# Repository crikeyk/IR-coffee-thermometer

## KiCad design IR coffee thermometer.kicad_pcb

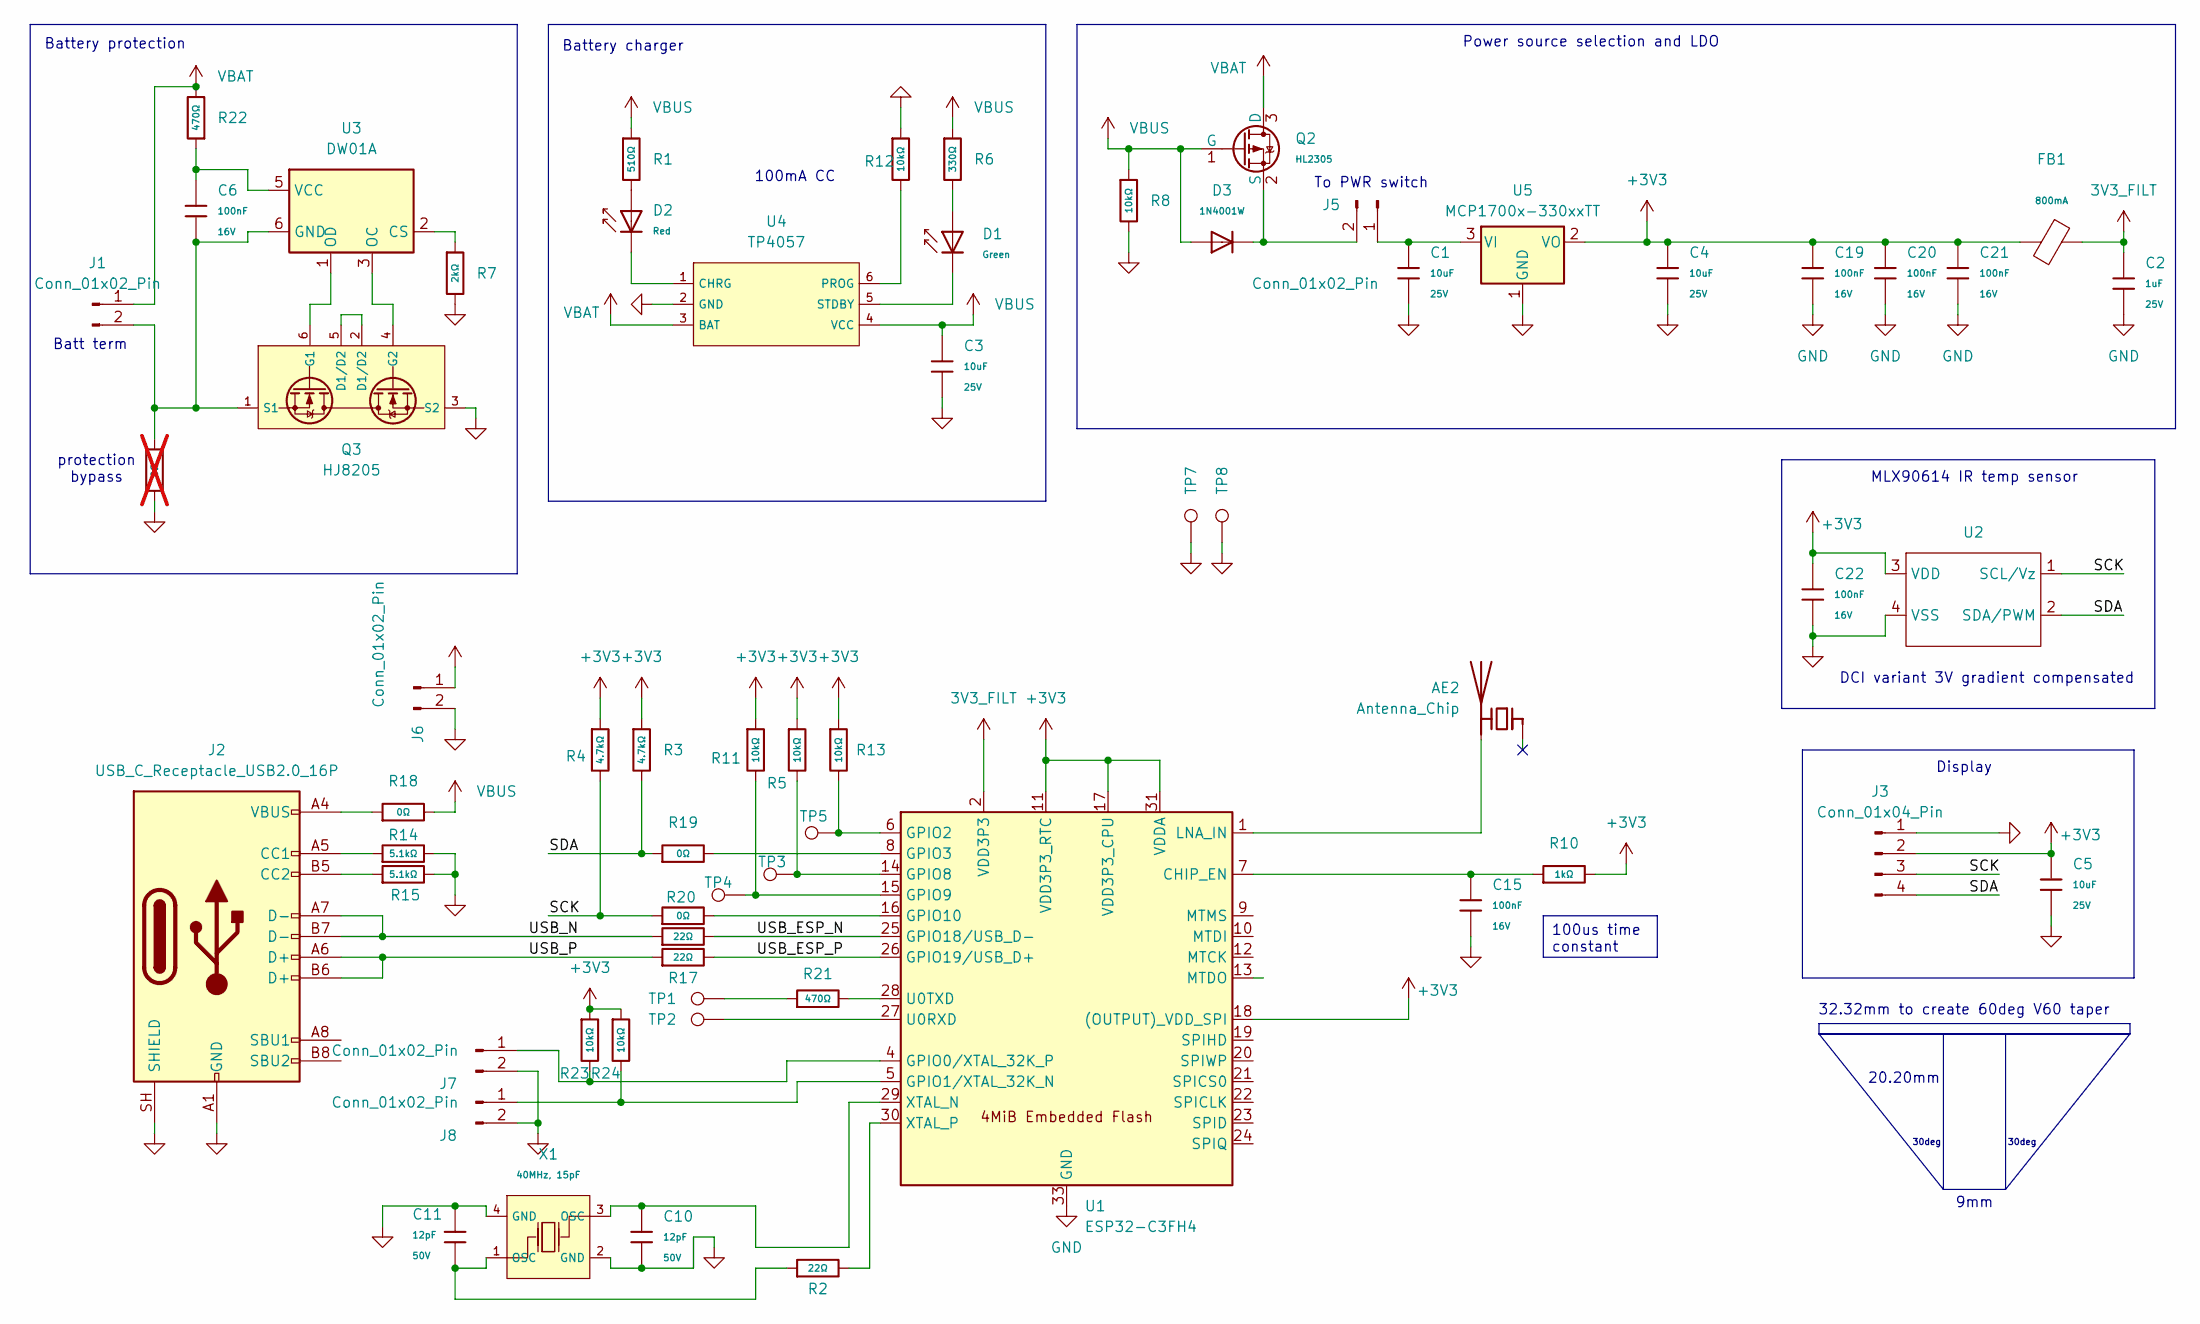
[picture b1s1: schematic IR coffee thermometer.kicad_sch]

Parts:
AE2: Antenna_Chip; C_1206_3216Metric; LCSC C127629
C1, C3, C4, C5: 10uF; C_0603; Voltage Rated 25V; Tolerance ±20%; Part CL10A106MA8NRNC; LCSC C96446
C2: 1uF; C_0402; Voltage Rated 25V; Tolerance ±10%; Part CL05A105KA5NQNC; LCSC C52923
C6, C15, C19, C20, C21, C22: 100nF; C_0402; Voltage Rated 16V; Tolerance ±10%; Part CL05B104KO5NNNC; LCSC C1525
C10, C11: 12pF; C_0402; Voltage Rated 50V; Tolerance ±5%; Part 0402CG120J500NT; LCSC C1547
D1: Green; D_0805; Part KT-0805G; LCSC C2297
D2: Red; D_0805; Forward Voltage (VF) 1.6V~2.6V; Part NCD0805R1; LCSC C84256
D3: 1N4001W; D_SOD-123FL; Voltage - Forward(Vf@If) 1V@1.0A; Voltage - DC Reverse(Vr) 50V; Part 1N4001W; LCSC C18199085
FB1: FB_0805; Current Rating 800mA; Tolerance ±25%; Part GZ2012D101TF; LCSC C1015
J1, J5, J6, J7, J8: Conn_01x02_Pin; TestPoint_2Pads_Pitch2.54mm_Drill0.8mm
J2: USB_C_Receptacle_USB2.0_16P; USB_C_Receptacle_HRO_TYPE-C-31-M-12; LCSC C165948
J3: Conn_01x04_Pin; PinSocket_1x04_P2.54mm_Vertical; LCSC C2718488
Q2: HL2305; Q_SOT-23; Part HL2305; LCSC C28646261
Q3: HJ8205; SOT-23-6_L2.9-W1.6-P0.95-LS2.8-BR; Part HJ8205; LCSC C20069150
R1: 510Ω; R_0402; Overload Voltage (Max) 50V; Tolerance ±1%; Part 0402WGF5100TCE; LCSC C25123
R2, R16, R17: 22Ω; R_0402; Overload Voltage (Max) 50V; Tolerance ±1%; Part 0402WGF220JTCE; LCSC C25092
R3, R4: 4.7kΩ; R_0402; Overload Voltage (Max) 50V; Tolerance ±1%; Part 0402WGF4701TCE; LCSC C25900
R5, R8, R11, R12, R13, R23, R24: 10kΩ; R_0402; Overload Voltage (Max) 50V; Tolerance ±1%; Part 0402WGF1002TCE; LCSC C25744
R6: 330Ω; R_0402; Overload Voltage (Max) 50V; Tolerance ±1%; Part 0402WGF3300TCE; LCSC C25104
R7: 2kΩ; R_0402; Overload Voltage (Max) 50V; Tolerance ±1%; Part 0402WGF2001TCE; LCSC C4109
R9: 0Ω; R_0402; Overload Voltage (Max) 50V; Tolerance ±1%; Part 0402WGF0000TCE; LCSC C17168; not fitted
R10: 1kΩ; R_0402; Overload Voltage (Max) 50V; Tolerance ±1%; Part 0402WGF1001TCE; LCSC C11702
R14, R15: 5.1kΩ; R_0402; Overload Voltage (Max) 50V; Tolerance ±1%; Part 0402WGF5101TCE; LCSC C25905
R18, R19, R20: 0Ω; R_0402; Overload Voltage (Max) 50V; Tolerance ±1%; Part 0402WGF0000TCE; LCSC C17168
R21, R22: 470Ω; R_0402; Overload Voltage (Max) 50V; Tolerance ±1%; Part 0402WGF4700TCE; LCSC C25117
TP1, TP2, TP3, TP4, TP5, TP7, TP8: TestPoint; TestPoint_Pad_D1.0mm
U1: ESP32-C3FH4; QFN-32-1EP_5x5mm_P0.5mm_EP3.7x3.7mm_ThermalVias; LCSC C2858491
U2: MLX90614
U3: DW01A; SOT-23-6; LCSC C18164398
U4: TP4057; SOT-23-6_L2.9-W1.6-P0.95-LS2.8-BL; Part TP4057-42-SOT26-R; LCSC C12044
U5: MCP1700x-330xxTT; SOT-23; LCSC C39051
X1: 40MHz, 15pF; OSC-SMD_4P-L3.2-W2.5-BL_SIT8008BI; PartID X322540MPB4SI; LCSC C9010

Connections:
3V3_FILT: C2.1, FB1.1, U1.2 (VDD3P3), U1.3 (VDD3P3)
+3V3: C4.1, C5.1, C19.1, C20.1, C21.1, C22.1, FB1.2, J3.2, R3.1, R4.1, R5.1, R10.2, R11.1, R13.1, R23.1, R24.1, U1.11 (VDD3P3_RTC), U1.17 (VDD3P3_CPU), U1.18 ((OUTPUT)_VDD_SPI), U1.31 (VDDA), U1.32 (VDDA), U2.3 (VDD), U5.2 (VO)
/SCK: J3.3, R4.2, R20.1, U2.1 (SCL/Vz)
/SDA: J3.4, R3.2, R19.1, U2.2 (SDA/PWM)
/USB_ESP_N: R16.2, U1.25 (GPIO18/USB_D-)
/USB_ESP_P: R17.2, U1.26 (GPIO19/USB_D+)
/USB_N: J2.A7 (D-), J2.B7 (D-), R16.1
/USB_P: J2.A6 (D+), J2.B6 (D+), R17.1
GND: C1.2, C2.2, C3.2, C4.2, C5.2, C10.2, C11.2, C15.2, C19.2, C20.2, C21.2, C22.2, J2.A1 (GND), J2.A12 (GND), J2.B1 (GND), J2.B12 (GND), J2.SH (SHIELD), J3.1, J6.2, J7.2, J8.2, Q3.3 (S2), R7.2, R8.2, R9.2, R12.1, R14.2, R15.2, TP7.1 (1_1), TP8.1 (1_1), U1.33 (GND), U2.4 (VSS), U4.2 (GND), U5.1 (GND), X1.2 (GND), X1.4 (GND)
unnamed: AE2.2 (PCB_Trace_2), U1.1 (LNA_IN)
unnamed: C11.1, R2.1, X1.1 (OSC)
unnamed: D1.2, R6.2
unnamed: D2.2, R1.2
unnamed: C6.2, J1.2, Q3.1 (S1), R9.1, U3.6 (GND)
unnamed: J2.A5 (CC1), R14.1
unnamed: J2.B5 (CC2), R15.1
unnamed: J2.A4 (VBUS), J2.A9 (VBUS), J2.B4 (VBUS), J2.B9 (VBUS), R18.1
unnamed: C1.1, J5.1, U5.3 (VI)
unnamed: D3.1, J5.2, Q2.2 (S)
unnamed: J7.1, R23.2, U1.4 (GPIO0/XTAL_32K_P)
unnamed: J8.1, R24.2, U1.5 (GPIO1/XTAL_32K_N)
unnamed: Q3.2 (D1/D2), Q3.5 (D1/D2)
unnamed: Q3.6 (G1), U3.1 (OD)
unnamed: Q3.4 (G2), U3.3 (OC)
unnamed: R21.1, TP1.1 (1_1)
unnamed: C15.1, R10.1, U1.7 (CHIP_EN)
unnamed 26: R13.2, TP5.1, U1.6 (GPIO2); also elsewhere on the board
unnamed: R19.2, U1.8 (GPIO3)
unnamed 28: R5.2, TP3.1, U1.14 (GPIO8); also elsewhere on the board
unnamed 29: R11.2, TP4.1, U1.15 (GPIO9); also elsewhere on the board
unnamed: R20.2, U1.16 (GPIO10)
unnamed: TP2.1 (1_1), U1.27 (U0RXD)
unnamed: R21.2, U1.28 (U0TXD)
unnamed: C10.1, U1.29 (XTAL_N), X1.3 (OSC)
unnamed: R2.2, U1.30 (XTAL_P)
unnamed: R7.1, U3.2 (CS)
unnamed: C6.1, R22.1, U3.5 (VCC)
unnamed: D2.1, U4.1 (CHRG)
unnamed: R12.2, U4.6 (PROG)
unnamed: D1.1, U4.5 (STDBY)
VBAT: J1.1, Q2.3 (D), R22.2, U4.3 (BAT)
VBUS: C3.1, D3.2, J6.1, Q2.1 (G), R1.1, R6.1, R8.1, R18.2, U4.4 (VCC)

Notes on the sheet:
30deg
DCI variant 3V gradient compensated
9mm
20.20mm
Power source selection and LDO
To PWR switch
100mA CC
Display
MLX90614 IR temp sensor
32.32mm to create 60deg V60 taper
Battery charger
protection bypass
Batt term
Battery protection
100us time constant

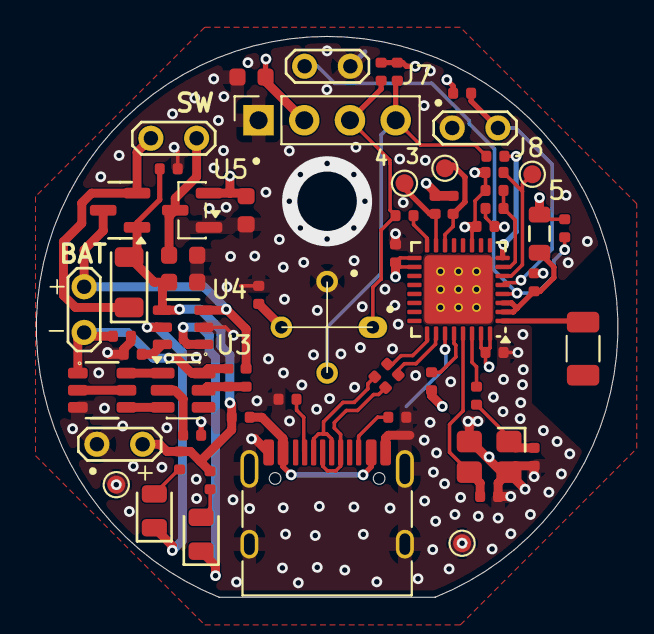
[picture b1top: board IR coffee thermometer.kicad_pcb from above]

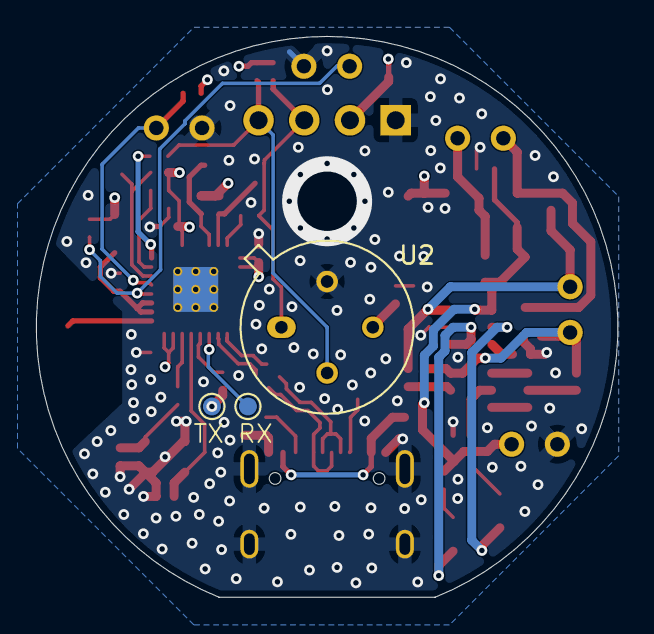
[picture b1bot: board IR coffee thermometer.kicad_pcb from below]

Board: 4 copper layers, 32.3 x 31.2 mm, 64 parts (3 on the bottom side), 42 nets.

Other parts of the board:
3, 4, 5: TestPoint; TestPoint_Pad_D1.0mm

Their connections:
unnamed 26: 5.1 (1_1); also elsewhere on the board
unnamed 28: 3.1 (1_1); also elsewhere on the board
unnamed 29: 4.1 (1_1); also elsewhere on the board

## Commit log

2026-05-21 Update README.md
    added image
2026-05-21 basic layout
2026-05-22 schematic complete
2026-05-28 routing complete
2026-05-30 gerber out
2026-05-30 release for fab
2026-05-31 added step files
2026-06-09 added PoC fw
2026-06-09 added webpage functionality
2026-06-13 added Wifi only on reboot. added graphing
2026-06-25 changed timeout for wifi to 1s
